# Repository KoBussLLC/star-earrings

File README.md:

# star-earrings

PCB earrings to show the world that you are there!

## Features

- 4 bright white LEDs
- Mode changing push button
- On/Off Switch
- CR1220 battery life estimated at 570 hours (40mAh/0.07mA)
- Open-source hardware and software allow customizable LED patterns

## Design Considerations

- As light weight as possible -> 0.8mm PCB Thickness
- Balance battery weight/life -> CR1220 Button Cell Battery
- Bright LEDs -> PWM controlled to avoid inline resistor
- Minimal aesthetic -> UFQFPN20 microcontroller footprint
- Power Saving -> STM32L011U6
- No loss of battery while in storage -> Slide switch for on/off
- Mode changing -> Push Button to switch LED patterns
- SMD Manufacturing/Assembly -> 100% SMD Components with dual side panelized assembly

## Firmware

The firmware for the earrings uses the open-source [libopencm3](http://libopencm3.org/) library

- TIM2 used for PWM
- TIM21 used for LED pattern changing interrupt
- EXTI4 Interrupt used for push button
- LPTIM1 used for button debounce

### Generate PWM Sine Waves

Short python3 script to generate breathing pattern array. Modify this script and TIM2 values to customize LED patterns

``` python
import numpy as np
import math

t = np.linspace(0.0, 2.0*math.pi, num=32)
max_ccr = 16.0 
np.set_printoptions(precision=0)
array = np.cos(t)*-1.0*max_ccr + max_ccr + 1.0
array = np.round(array).astype(int)

print(np.array2string(array, formatter={'int':lambda x: str(x)}, separator=', '))
```

## Customer Instructions

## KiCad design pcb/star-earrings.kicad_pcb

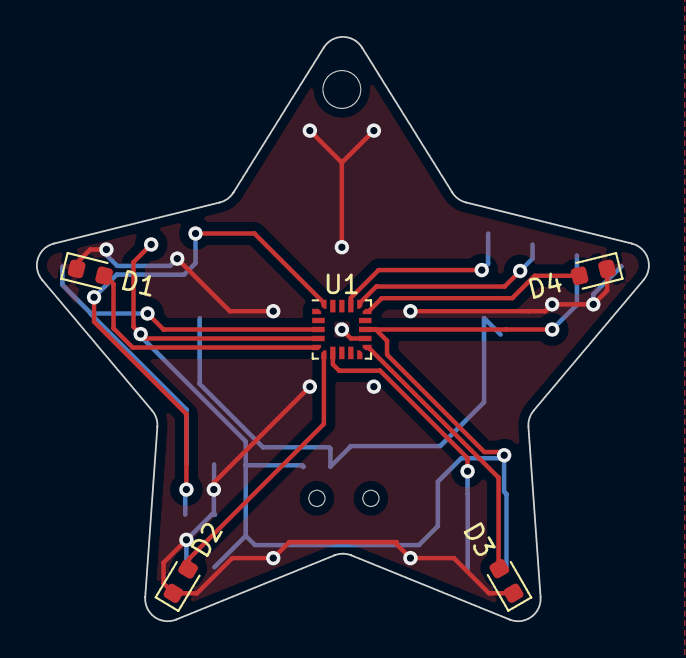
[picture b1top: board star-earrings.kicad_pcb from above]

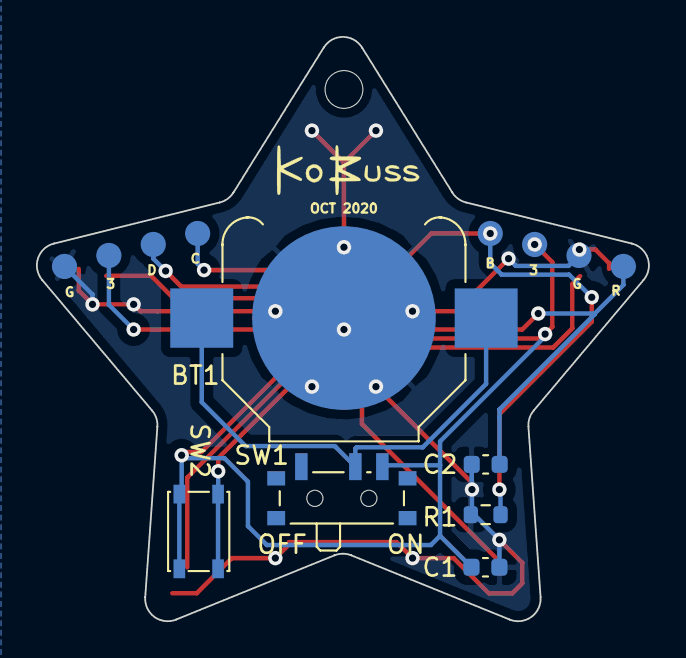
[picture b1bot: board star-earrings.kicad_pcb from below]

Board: 2 copper layers, 34.0 x 32.5 mm, 15 parts (10 on the bottom side), 12 nets.

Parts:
BT1: Battery_Cell; BatteryHolder_Keystone_3000_1x12mm
C1: 10uF; C_0603_1608Metric
C2: 100nF; C_0603_1608Metric
D1, D2, D3, D4: LED; LED_0603_1608Metric
H1: MountingHole; MountingHole_2.1mm
J1, J2: Conn_01x04_Pad; TestPoint_4Pads_Pitch2.54mm
R1: 10k; R_0603_1608Metric
Ref**: Val**; kobuss_name_s
SW1: SW_SPDT; SW_SPDT_PCM12
SW2: SW_SPST; SW_SPST_PTS810
U1: STM32L011F4Ux; ST_UFQFPN-20_3x3mm_P0.5mm

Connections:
+3V0: C1.1, J1.3, J2.2, SW1.3, SW2.1, U1.4, U1.13
+BATT: BT1.1, SW1.2
GND: BT1.2, C1.2, C2.1, D1.1, D2.1, D3.1, D4.1, J1.4, J2.3, R1.2, U1.12
LED0: D1.2, U1.5
LED1: D2.2, U1.6
LED2: D3.2, U1.11
LED3: D4.2, U1.15
unnamed: C2.2, J2.4, U1.3
unnamed: J2.1, R1.1, U1.20
SWCLK: J1.1, U1.17
SWDIO: J1.2, U1.16
SWITCH: SW2.2, U1.7

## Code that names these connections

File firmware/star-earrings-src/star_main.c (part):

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#define LED_PORT GPIOC
#endif

#define LED0_PORT GPIOA
#define LED0_PIN GPIO0
#define LED1_PORT GPIOA
#define LED1_PIN GPIO1
#define LED2_PORT GPIOB
#define LED2_PIN GPIO1
#define LED3_PORT GPIOA
#define LED3_PIN GPIO10

#define BTN_PORT GPIOA
#define BTN_PIN GPIO4
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    gpio_mode_setup(LED_PORT, GPIO_MODE_OUTPUT, GPIO_PUPD_NONE, LED_PIN);
#endif

    gpio_mode_setup(LED0_PORT, GPIO_MODE_AF, GPIO_PUPD_NONE, LED0_PIN);
    gpio_mode_setup(LED1_PORT, GPIO_MODE_AF, GPIO_PUPD_NONE, LED1_PIN);
    gpio_mode_setup(LED2_PORT, GPIO_MODE_AF, GPIO_PUPD_NONE, LED2_PIN);
    gpio_mode_setup(LED3_PORT, GPIO_MODE_AF, GPIO_PUPD_NONE, LED3_PIN);

    gpio_set_af(LED0_PORT, GPIO_AF2, LED0_PIN);
    gpio_set_af(LED1_PORT, GPIO_AF2, LED1_PIN);
    gpio_set_af(LED2_PORT, GPIO_AF5, LED2_PIN);
    gpio_set_af(LED3_PORT, GPIO_AF5, LED3_PIN);

    gpio_set_output_options(LED0_PORT, GPIO_OTYPE_PP, GPIO_OSPEED_LOW, LED0_PIN);
    gpio_set_output_options(LED1_PORT, GPIO_OTYPE_PP, GPIO_OSPEED_LOW, LED1_PIN);
    gpio_set_output_options(LED2_PORT, GPIO_OTYPE_PP, GPIO_OSPEED_LOW, LED2_PIN);
    gpio_set_output_options(LED3_PORT, GPIO_OTYPE_PP, GPIO_OSPEED_LOW, LED3_PIN);

    // TIM2 Setup for PWM on all channels
    timer_set_mode(TIM2, TIM_CR1_CKD_CK_INT, TIM_CR1_CMS_EDGE, TIM_CR1_DIR_UP);
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
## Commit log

2020-11-06 Add libopencm3 submodule
2020-11-06 Initial earring firmware
2020-11-07 Button debounce implemented
2020-11-07 LED Breathing Pattern Default
2020-11-13 Hardware V0
2020-11-17 V1 firmware update with fixture CAD
2020-12-05 Added customer instructions
2020-12-05 fixed offset of image
2020-12-07 Added battery insertion step
2020-12-07 fixed battery plus sign
2021-06-29 doc: README typo
